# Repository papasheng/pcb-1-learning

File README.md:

# pcb#1-learning
 First PCB, learning via ai03 guide

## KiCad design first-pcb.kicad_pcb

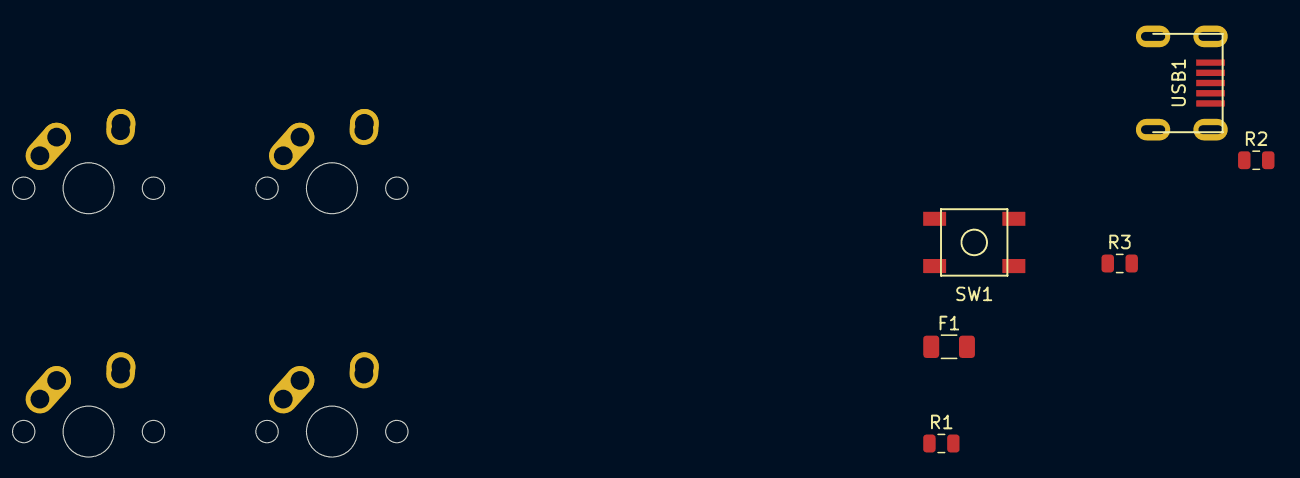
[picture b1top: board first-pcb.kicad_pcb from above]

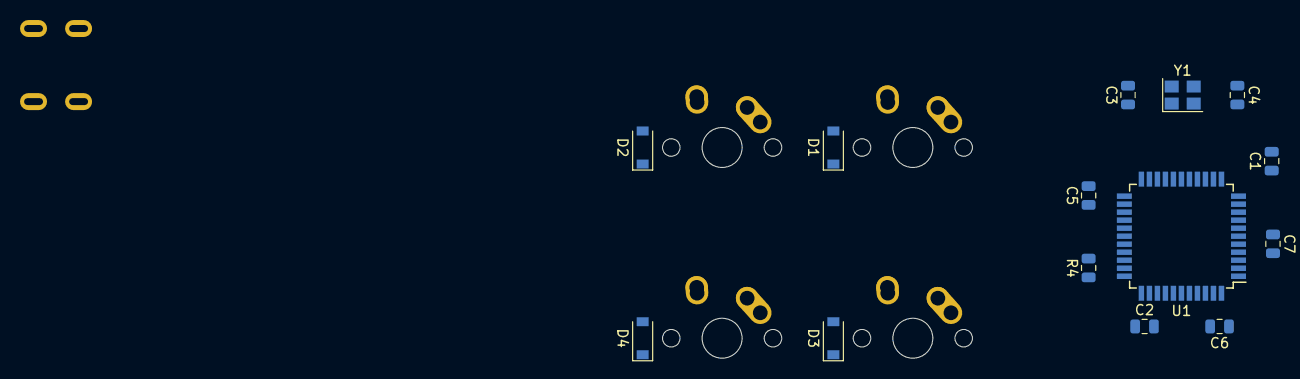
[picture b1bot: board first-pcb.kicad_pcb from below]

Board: 2 copper layers, 24 parts (14 on the bottom side), 20 nets, no tracks yet.

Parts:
C1, C2, C5: 0.1uF; C_0805_2012Metric
C3, C4: 22pF; C_0805_2012Metric
C6: 10uF; C_0805_2012Metric
C7: C_Small; C_0805_2012Metric
D1, D2, D3, D4: D_Small; D_SOD-123
F1: 500mA; Fuse_1206_3216Metric
MX1, MX2, MX3, MX4: MX-NoLED; MX-1U-NoLED
R1, R2: 22; R_0805_2012Metric
R3, R4: 10k; R_0805_2012Metric
SW1: SW_Push; SKQG-1155865
U1: ATmega32U4-AU; TQFP-44_10x10mm_P0.8mm
USB1: Molex-0548190589
Y1: 16MHz; Crystal_SMD_3225-4Pin_3.2x2.5mm

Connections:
+5V: C1.1, C2.1, C5.1, C6.1, F1.1, R3.1, U1.2, U1.7, U1.14, U1.24, U1.34, U1.44
COL0: MX1.1, MX3.1
COL1: MX2.1, MX4.1
D+: R2.2, USB1.3
D-: R1.2, USB1.4
GND: C1.2, C2.2, C3.2, C4.2, C5.2, C6.2, C7.2, R4.1, SW1.1, U1.5, U1.15, U1.23, U1.35, U1.43, USB1.1, Y1.2, Y1.4
unnamed: C3.1, U1.17, Y1.1
unnamed: C4.1, U1.16, Y1.3
unnamed: C7.1, U1.6
unnamed: D1.2, MX1.2
unnamed: D2.2, MX2.2
unnamed: D3.2, MX3.2
unnamed: D4.2, MX4.2
unnamed: R1.1, U1.3
unnamed: R2.1, U1.4
unnamed: R3.2, SW1.2, U1.13
unnamed: R4.2, U1.33
ROW0: D1.1, D2.1
ROW1: D3.1, D4.1
VCC: F1.2, USB1.5

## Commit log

2021-03-16 kiCad Project Initialised
2021-03-16 Add submodules
2021-03-16 Added footprint libraries
2021-03-17 part 3 started
    Up to, but not including decoupling capacitors
2021-03-18 MCU schematic zone complete
2021-03-19 Sch Done
2021-03-19 Footprint assigned
    Can begin pcb
2021-03-24 PCB Started
